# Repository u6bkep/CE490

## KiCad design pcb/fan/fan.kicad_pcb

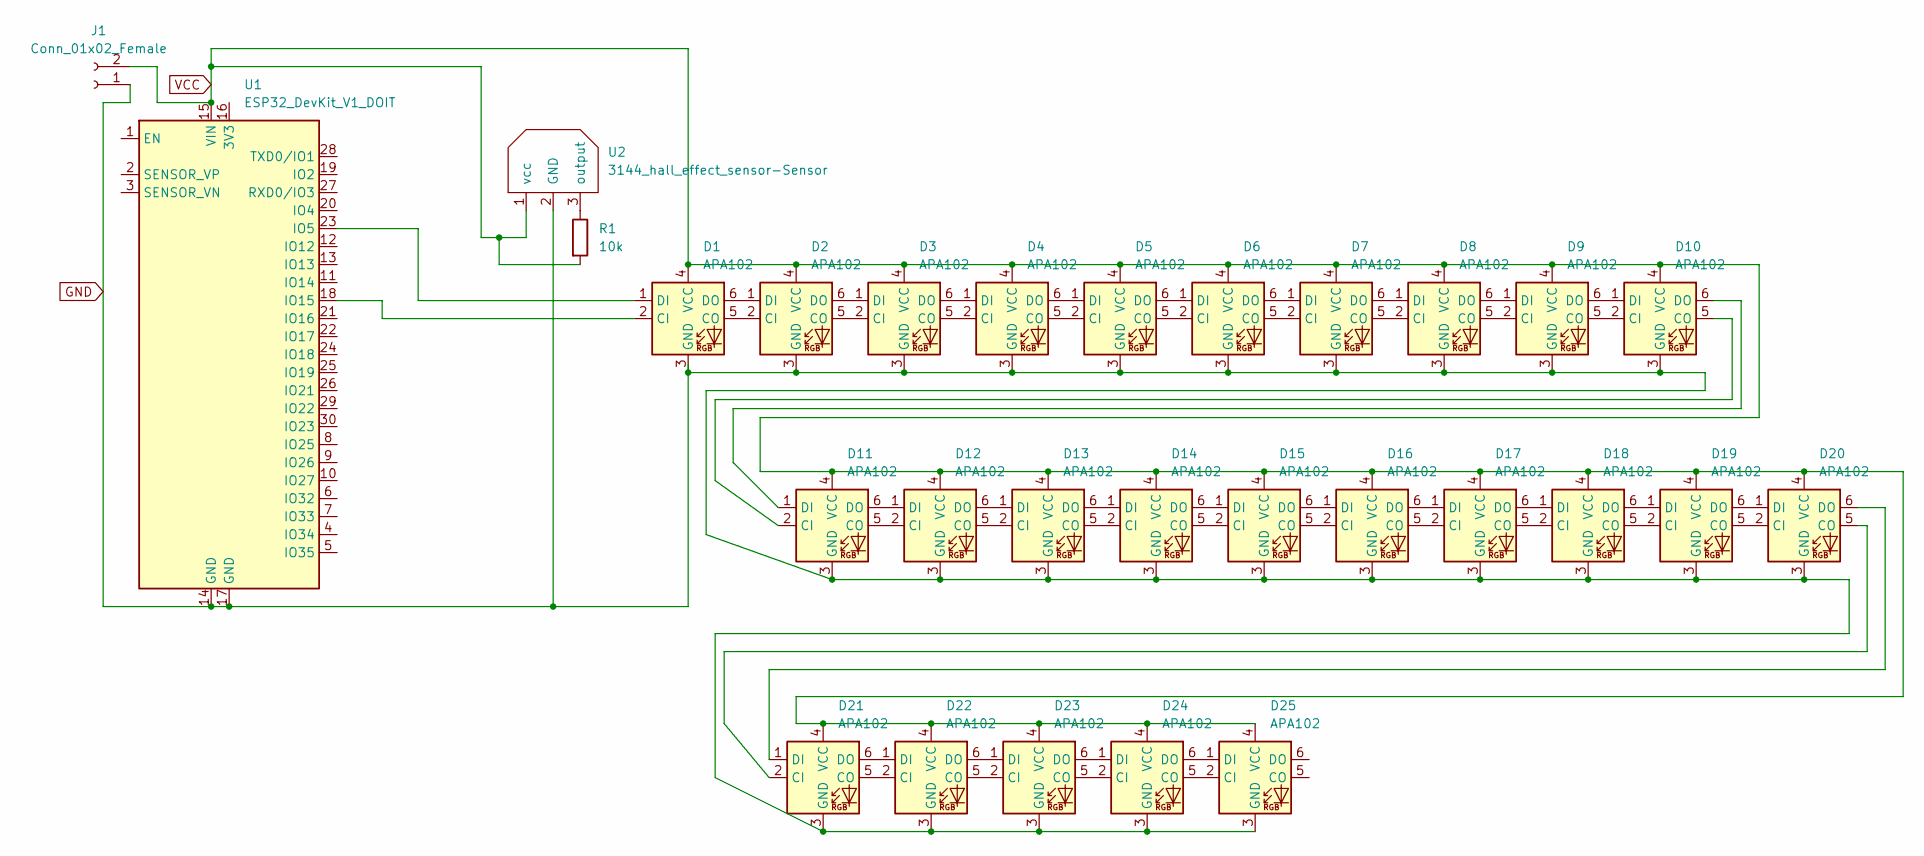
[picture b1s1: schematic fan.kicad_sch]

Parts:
D1, D2, D3, D4, D5, D6, D7, D8, D9, D10, D11, D12, D13, D14, D15, D16, D17, D18, D19, D20, D21, D22, D23, D24, D25: APA102; LED_RGB_5050-6
J1: Conn_01x02_Female; PinHeader_1x02_P2.54mm_Vertical
R1: 10k; R_0603_1608Metric
U1: ESP32_DevKit_V1_DOIT; esp32_devkit_v1_doit
U2: 3144_hall_effect_sensor-Sensor; TO-92Flat

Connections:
GND: D1.3 (GND), D2.3 (GND), D3.3 (GND), D4.3 (GND), D5.3 (GND), D6.3 (GND), D7.3 (GND), D8.3 (GND), D9.3 (GND), D10.3 (GND), D11.3 (GND), D12.3 (GND), D13.3 (GND), D14.3 (GND), D15.3 (GND), D16.3 (GND), D17.3 (GND), D18.3 (GND), D19.3 (GND), D20.3 (GND), D21.3 (GND), D22.3 (GND), D23.3 (GND), D24.3 (GND), D25.3 (GND), J1.1, U1.14 (GND), U1.17 (GND), U2.2 (GND)
unnamed: D1.1 (DI), U1.23 (IO5)
unnamed: D1.2 (CI), U1.18 (IO15)
unnamed: D1.5 (CO), D2.2 (CI)
unnamed: D1.6 (DO), D2.1 (DI)
unnamed: D2.5 (CO), D3.2 (CI)
unnamed: D2.6 (DO), D3.1 (DI)
unnamed: D3.5 (CO), D4.2 (CI)
unnamed: D3.6 (DO), D4.1 (DI)
unnamed: D4.5 (CO), D5.2 (CI)
unnamed: D4.6 (DO), D5.1 (DI)
unnamed: D5.5 (CO), D6.2 (CI)
unnamed: D5.6 (DO), D6.1 (DI)
unnamed: D6.5 (CO), D7.2 (CI)
unnamed: D6.6 (DO), D7.1 (DI)
unnamed: D7.5 (CO), D8.2 (CI)
unnamed: D7.6 (DO), D8.1 (DI)
unnamed: D8.5 (CO), D9.2 (CI)
unnamed: D8.6 (DO), D9.1 (DI)
unnamed: D9.6 (DO), D10.1 (DI)
unnamed: D9.5 (CO), D10.2 (CI)
unnamed: D10.5 (CO), D11.2 (CI)
unnamed: D10.6 (DO), D11.1 (DI)
unnamed: D11.5 (CO), D12.2 (CI)
unnamed: D11.6 (DO), D12.1 (DI)
unnamed: D12.5 (CO), D13.2 (CI)
unnamed: D12.6 (DO), D13.1 (DI)
unnamed: D13.5 (CO), D14.2 (CI)
unnamed: D13.6 (DO), D14.1 (DI)
unnamed: D14.5 (CO), D15.2 (CI)
unnamed: D14.6 (DO), D15.1 (DI)
unnamed: D15.5 (CO), D16.2 (CI)
unnamed: D15.6 (DO), D16.1 (DI)
unnamed: D16.5 (CO), D17.2 (CI)
unnamed: D16.6 (DO), D17.1 (DI)
unnamed: D17.5 (CO), D18.2 (CI)
unnamed: D17.6 (DO), D18.1 (DI)
unnamed: D18.5 (CO), D19.2 (CI)
unnamed: D18.6 (DO), D19.1 (DI)
unnamed: D19.5 (CO), D20.2 (CI)
unnamed: D19.6 (DO), D20.1 (DI)
unnamed: D20.5 (CO), D21.2 (CI)
unnamed: D20.6 (DO), D21.1 (DI)
unnamed: D21.5 (CO), D22.2 (CI)
unnamed: D21.6 (DO), D22.1 (DI)
unnamed: D22.5 (CO), D23.2 (CI)
unnamed: D22.6 (DO), D23.1 (DI)
unnamed: D23.5 (CO), D24.2 (CI)
unnamed: D23.6 (DO), D24.1 (DI)
unnamed: D24.5 (CO), D25.2 (CI)
unnamed: D24.6 (DO), D25.1 (DI)
unnamed: R1.1, U2.3 (output)
VCC: D1.4 (VCC), D2.4 (VCC), D3.4 (VCC), D4.4 (VCC), D5.4 (VCC), D6.4 (VCC), D7.4 (VCC), D8.4 (VCC), D9.4 (VCC), D10.4 (VCC), D11.4 (VCC), D12.4 (VCC), D13.4 (VCC), D14.4 (VCC), D15.4 (VCC), D16.4 (VCC), D17.4 (VCC), D18.4 (VCC), D19.4 (VCC), D20.4 (VCC), D21.4 (VCC), D22.4 (VCC), D23.4 (VCC), D24.4 (VCC), D25.4 (VCC), J1.2, R1.2, U1.15 (VIN), U2.1 (vcc)

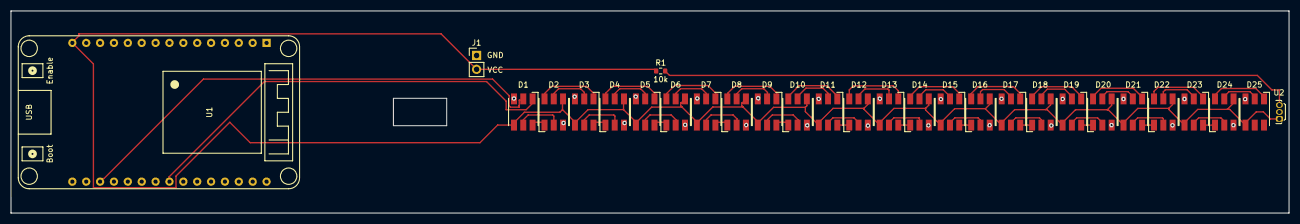
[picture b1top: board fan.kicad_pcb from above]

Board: 2 copper layers, 234.0 x 37.0 mm, 29 parts (0 on the bottom side), 53 nets.

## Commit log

2022-01-24 initial commit
    initial commit containing basic directory structure and template KiCad template.
2022-01-25 added esp32 documentatino and footprint library from old revision
2022-01-25 Remote Schematic
    Schematic made for POV Fan remote. Contains an ESP 32 Microcontroller, 5 Push Buttons, and a resistor.
2022-01-25 Update Remote.kicad_sch
    Added a couple description to better code later down the line
2022-01-28 Code for the remote Controller
    Established wireless communication between boards, code to check if buttons work, and code to obtain mac address of boards.
2022-02-02 Attempt to make button values work across communication
    it does not work
2022-02-04 made fan blade pcb fit for 25 LEDs
2022-02-04 minor adjust length, added solder pads
2022-02-08 added gerber files for pbc
    also committing motor mount STLs and prototyping code.
    added esp-idf stuff to gitignore
    added idf dotstar library as submodule
2022-02-18 Updated code
2022-02-18 Update Remote.kicad_sch
    Updated the Pins in the schematics
2022-02-18 Framing Motor Code
2022-02-18 rearranged directory
2022-02-18 motor code
2022-02-18 motor code debugging
2022-02-18 add bitmask calculation demo add pwm demo add deliverables and ethics report
2022-02-25 added in character codes
2022-02-25 added more special chars
2022-02-25 added esp32servo demo cleanup of prototypeing folder
2022-02-25 finished chars
2022-03-01 servo demo
2022-03-01 updated fanblade code
2022-03-01 killed the code into pieces
2022-03-08 Update Motor.ino
    Changed speeds of motor to not run as fast. Added global variable so speeds are not hard codded.
2022-03-13 ignore bad apple frame breakouts and python virtual environments
2022-03-13 added working png decoding added standards report fixed strand test
2022-03-13 added sample header file, and changes made to fanPCB
2022-03-14 motor controller: - changed message data types to bool to match other software remote: - fixed many bugs... fanpcb: - ported project over to platformio in fanpcbv2 folder - added png rendering librar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
2022-03-16 got into working state for submission, then felt the need to break without committing. this branch has a mostly broken fix for all of the non thread safe behavior.
2022-03-16 finished recovering from my own stupidity
2022-09-25 added BOM
